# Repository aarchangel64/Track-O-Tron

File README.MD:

# Track-O-Tron
Track-O-Tron is a full-body VR tracking solution that uses LSM9DS1 Inertial Measurement Units (IMUs) integrated into clothing for inside-out full-body tracking.

This project was created as a Semester Long Design Project for NYU Tandon's EG-1003 course.

## Requirements
- [PlatformIO](https://platformio.org/platformio-ide) for compiling the Arduino code
- CMake for compiling the PC code

## Building
### PlatformIO (Arduino)
Enter the platformio/ subdirectory and open it in your PlatformIO IDE of choice, or build it using the PlatformIO CLI.

## Circuit Wiring

Connect each IMU's SPI pins to the hardware SPI pins on your microcontroller (pins 50, 51, and 52 for the Arduino Mega pictured above).
All IMUs share a single SPI bus, so all MOSI pins from every IMU will be connected together, and likewise for all MISO pins.
_Note that there are two MISO pins on LSM9DS1s for accel/gyro and mag, **both** of these lines will be connected together!_

In order for multiple peripherals to share an SPI bus like this, Chip Select (CS) lines are controlled by the MCU, so that only one IMU at a time will be communicating over SPI.
Connect each IMU's seperate accelerometer/gyroscope and magnetometer CS pins to their own digital pin on the MCU.

Make sure to update the ['imus' array in platformIO/src/main.cpp](platformio/src/main.cpp#L19) to match which CS pins you are using! 
The CS pin order is `{accel_cs_pin_, mag_cs_pin}`. 
So the array for the schematic above looks like this:

```c++
LSM imus[] = {
    {28, 27}, // IMU 0, which could be e.g. forearm_r
    {30, 29}, // IMU 1, which could be e.g. forearm_l
    {32, 31}, // IMU 2
    {34, 33}, // IMU 3
    {36, 35}  // IMU 4
};
```

See LSM9DS1 module documentation from [Adafruit](https://learn.adafruit.com/adafruit-lsm9ds1-accelerometer-plus-gyro-plus-magnetometer-9-dof-breakout/pinouts#spi-pins-2197900-7) and [Sparkfun](https://learn.sparkfun.com/tutorials/lsm9ds1-breakout-hookup-guide/all#hardware-hookup) for more details.

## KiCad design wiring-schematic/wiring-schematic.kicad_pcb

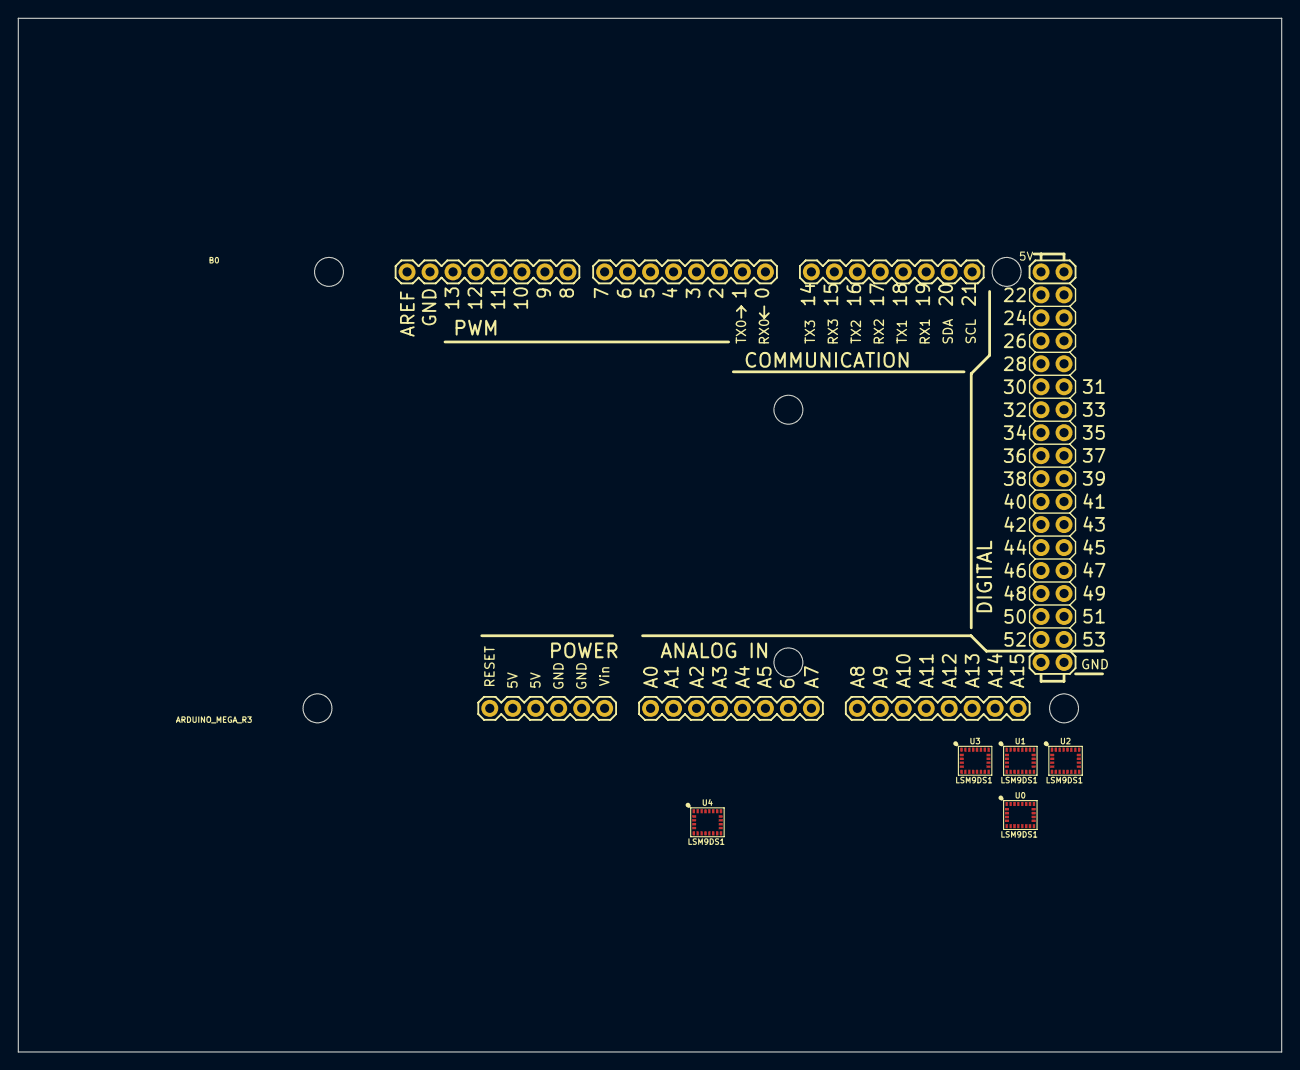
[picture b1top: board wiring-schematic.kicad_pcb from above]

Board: 2 copper layers, 139.7 x 114.3 mm, 6 parts (0 on the bottom side), 24 nets, no tracks yet.

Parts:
B0: ARDUINO_MEGA_R3; ARDUINO_MEGA
U0, U1, U2, U3, U4: LSM9DS1; LGA-24-3.5X3

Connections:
5V: B0.VIN, U0.22 (VDD), U0.23 (VDD), U1.22 (VDD), U1.23 (VDD), U2.22 (VDD), U2.23 (VDD), U3.22 (VDD), U3.23 (VDD), U4.22 (VDD), U4.23 (VDD)
/CS_ACC_0: B0.28, U0.7 (CS_A/G)
/CS_ACC_1: B0.30, U1.7 (CS_A/G)
/CS_ACC_2: B0.32, U2.7 (CS_A/G)
/CS_ACC_3: B0.34, U3.7 (CS_A/G)
/CS_ACC_4: B0.36, U4.7 (CS_A/G)
/CS_MAG_0: B0.27, U0.8 (CS_M)
/CS_MAG_1: B0.29, U1.8 (CS_M)
/CS_MAG_2: B0.31, U2.8 (CS_M)
/CS_MAG_3: B0.33, U3.8 (CS_M)
/CS_MAG_4: B0.35, U4.8 (CS_M)
/SPI_MOSI: B0.51 (51_(MOSI)), U0.4 (SDA/SDI/SDO), U1.4 (SDA/SDI/SDO), U2.4 (SDA/SDI/SDO), U3.4 (SDA/SDI/SDO), U4.4 (SDA/SDI/SDO)
/SPI_SCK: B0.52 (52_(SCK)), U0.2 (SCL/SPC), U1.2 (SCL/SPC), U2.2 (SCL/SPC), U3.2 (SCL/SPC), U4.2 (SCL/SPC)
GND: B0.GND@ (GND), U0.19 (GND), U0.20 (GND), U1.19 (GND), U1.20 (GND), U2.19 (GND), U2.20 (GND), U3.19 (GND), U3.20 (GND), U4.19 (GND), U4.20 (GND)
unnamed: U0.1 (VDDIO), U0.3 (VDDIO)
unnamed: U0.14 (RES), U0.15 (RES), U0.16 (RES), U0.17 (RES), U0.18 (RES)
unnamed: U1.1 (VDDIO), U1.3 (VDDIO)
unnamed: U1.14 (RES), U1.15 (RES), U1.16 (RES), U1.17 (RES), U1.18 (RES)
unnamed: U2.1 (VDDIO), U2.3 (VDDIO)
unnamed: U2.14 (RES), U2.15 (RES), U2.16 (RES), U2.17 (RES), U2.18 (RES)
unnamed: U3.1 (VDDIO), U3.3 (VDDIO)
unnamed: U3.14 (RES), U3.15 (RES), U3.16 (RES), U3.17 (RES), U3.18 (RES)
unnamed: U4.1 (VDDIO), U4.3 (VDDIO)
unnamed: U4.14 (RES), U4.15 (RES), U4.16 (RES), U4.17 (RES), U4.18 (RES)

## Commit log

2021-04-01 Inital platformIO code
2021-04-01 Setting up pc code
2021-04-01 Added README
2021-04-01 Added wiring diagram
2021-04-05 updated fritzing schematic
2021-04-05 added kicad project
2021-04-05 reorganised kicad schematic
2021-04-05 Finalised kicad schematic, and exported SVG
2021-04-05 Updated README with wiring information
2021-04-05 Added more information to README
2021-04-06 Updated kicad schematic to include missing MISO line
2021-04-06 Updated platformIO imus[] array to match kicad schematic
2021-04-06 Added extra info about SPI wiring to README
2021-04-06 Added fake SLDP company name to kicad schematic
2021-04-06 Removed fritzing diagramme & updated kicad info
2021-04-06 minor tweaks to kicad schematic positioning
2021-04-15 Inital Raspberry Pi code for measuring IMU data and sending it to a PC over the network (TCP)
2021-04-15 Inital testing rust code, not sure if it'll be used anymore since switching to sockets on RPi instead of serial on Arduino
2021-04-15 Moved kicad schematic into its own folder
2021-04-15 Updated KiCad schematic to use Raspberry Pi. TODO: update readme for RPi wiringdetails
